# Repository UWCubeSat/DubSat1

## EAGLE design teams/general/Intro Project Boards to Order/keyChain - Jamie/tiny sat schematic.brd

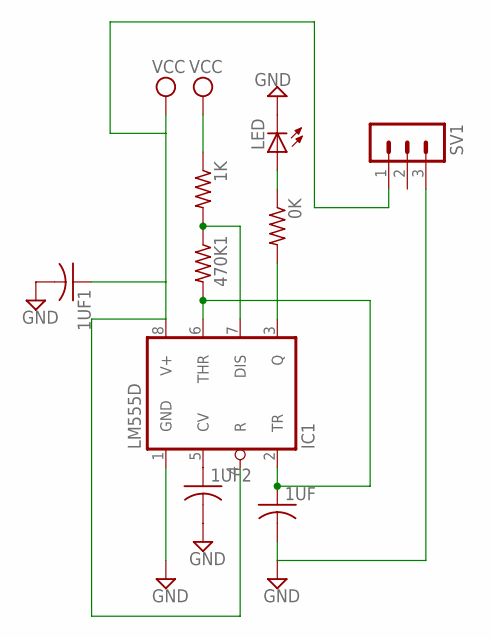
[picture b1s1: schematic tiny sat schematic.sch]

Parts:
0K, 1K, 470K1: R-US_R0805; R0805
1UF, 1UF1, 1UF2: C-USC0805; C0805
IC1: LM555D; SO08
LED: LED_ELD260; LED_LD260
SV1: MA03-1

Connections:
0: 1UF.1, 470K1.2, IC1.2 (TR), IC1.6 (THR)
470K: 0K.2, IC1.3 (Q)
GND: 1UF.2, 1UF1.2, 1UF2.2, IC1.1 (GND), LED.K (C), SV1.3
unnamed: 1K.2, 470K1.1, IC1.7 (DIS)
unnamed: 1UF2.1, IC1.5 (CV)
unnamed: 0K.1, LED.A
VCC: 1K.1, 1UF1.1, IC1.4 (R), IC1.8 (V+), SV1.1

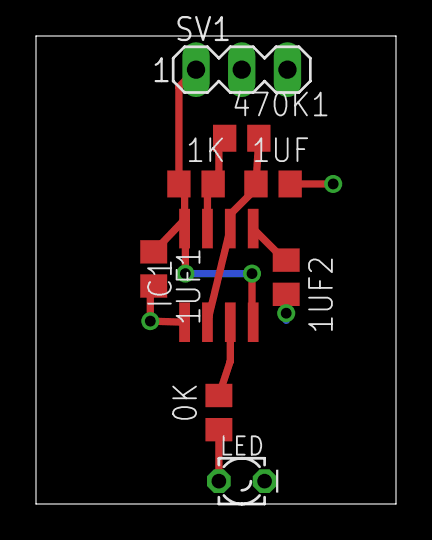
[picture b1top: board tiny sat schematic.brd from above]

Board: 2 copper layers, 20.0 x 26.0 mm, 9 parts (0 on the bottom side), 7 nets.

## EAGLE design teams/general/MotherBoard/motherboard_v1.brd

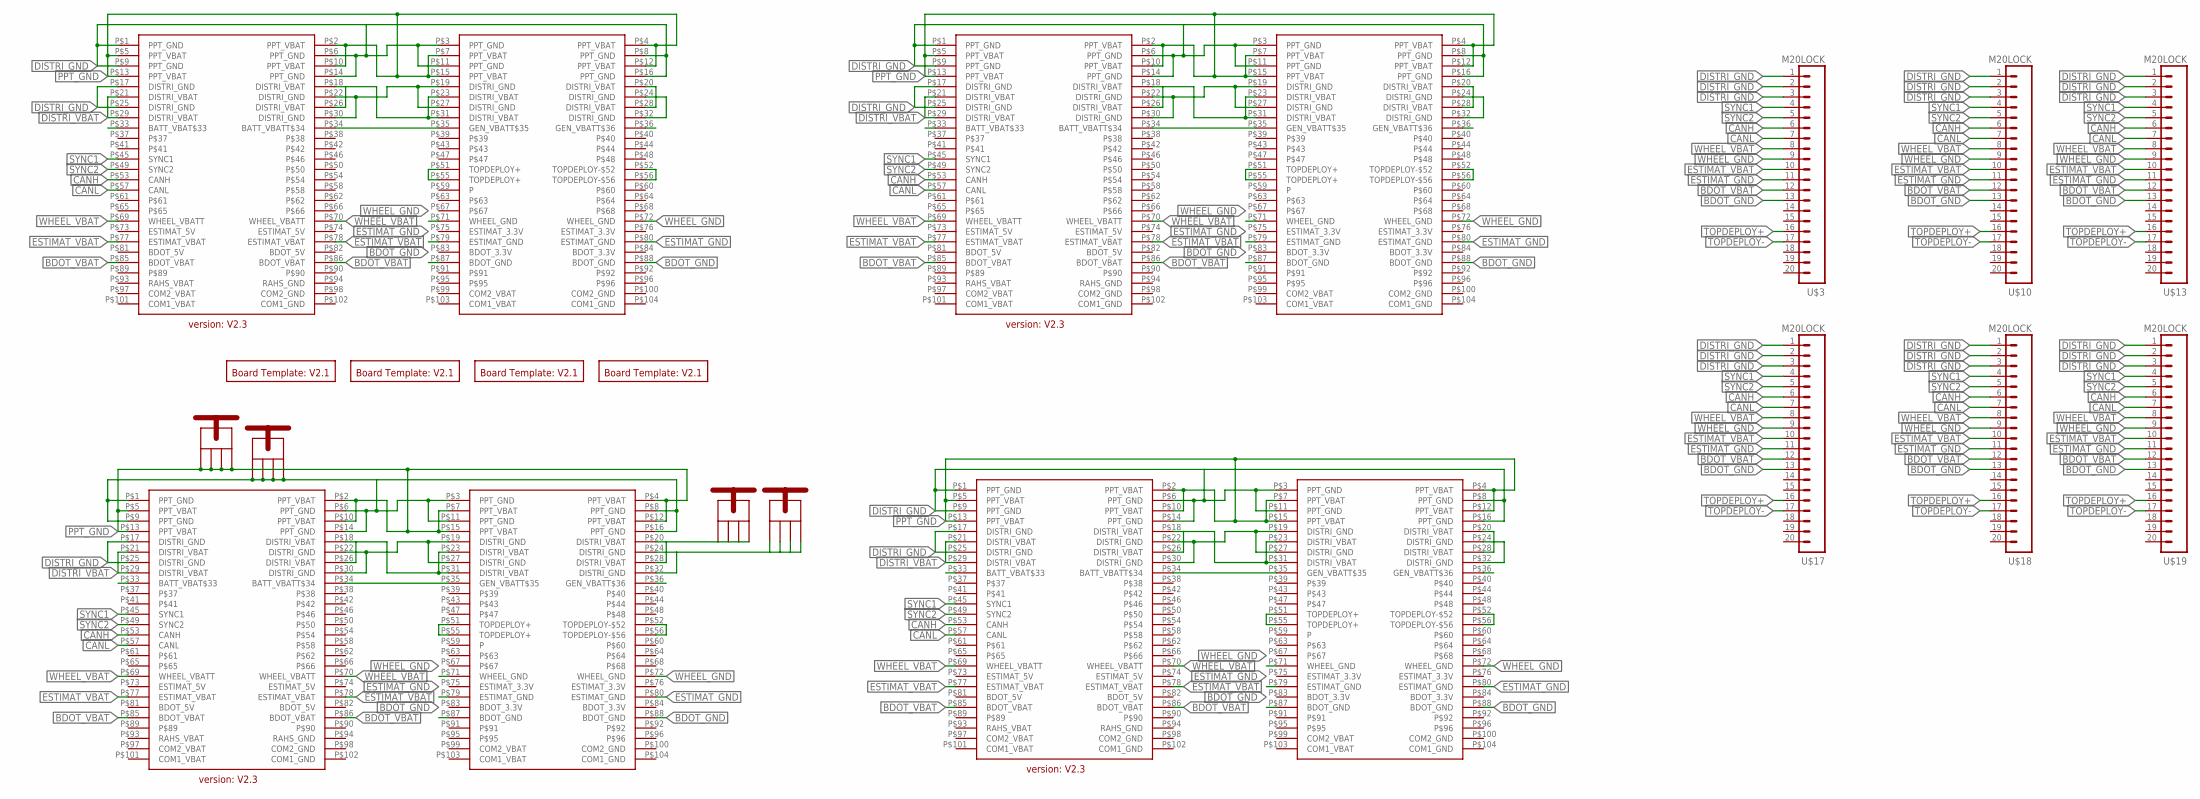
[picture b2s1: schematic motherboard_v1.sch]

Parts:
JP1, JP2, JP9, JP10: KEYSTONE_SCREW_TERMINAL_7701; 7701
U$1, U$4, U$5, U$6: BOARD_TEMPLATESILKONLY; BOARD_TEMPLATE_SILKONLY
U$2, U$7, U$9, U$11: PC104_CONNECTOR
U$3, U$10, U$13, U$17, U$18, U$19: M20LOCK; 1X20_LOCK

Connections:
BDOT_GND: U$2.P$87 (BDOT_GND), U$2.P$88 (BDOT_GND), U$3.13, U$7.P$87 (BDOT_GND), U$7.P$88 (BDOT_GND), U$9.P$87 (BDOT_GND), U$9.P$88 (BDOT_GND), U$10.13, U$11.P$87 (BDOT_GND), U$11.P$88 (BDOT_GND), U$13.13, U$17.13, U$18.13, U$19.13
BDOT_VBAT: U$2.P$85 (BDOT_VBAT), U$2.P$86 (BDOT_VBAT), U$3.12, U$7.P$85 (BDOT_VBAT), U$7.P$86 (BDOT_VBAT), U$9.P$85 (BDOT_VBAT), U$9.P$86 (BDOT_VBAT), U$10.12, U$11.P$85 (BDOT_VBAT), U$11.P$86 (BDOT_VBAT), U$13.12, U$17.12, U$18.12, U$19.12
CANH: U$2.P$53 (CANH), U$3.6, U$7.P$53 (CANH), U$9.P$53 (CANH), U$10.6, U$11.P$53 (CANH), U$13.6, U$17.6, U$18.6, U$19.6
CANL: U$2.P$57 (CANL), U$3.7, U$7.P$57 (CANL), U$9.P$57 (CANL), U$10.7, U$11.P$57 (CANL), U$13.7, U$17.7, U$18.7, U$19.7
DISTRI_GND: JP2.P$1, JP2.P$2, JP2.P$3, JP2.P$4, JP10.P$1, JP10.P$2, JP10.P$3, JP10.P$4, U$2.P$1 (PPT_GND), U$2.P$3 (PPT_GND), U$2.P$6 (PPT_GND), U$2.P$8 (PPT_GND), U$2.P$9 (PPT_GND), U$2.P$11 (PPT_GND), U$2.P$14 (PPT_GND), U$2.P$16 (PPT_GND), U$2.P$17 (DISTRI_GND), U$2.P$19 (DISTRI_GND), U$2.P$22 (DISTRI_GND), U$2.P$24 (DISTRI_GND), U$2.P$25 (DISTRI_GND), U$2.P$27 (DISTRI_GND), U$2.P$30 (DISTRI_GND), U$2.P$32 (DISTRI_GND), U$3.1, U$3.2, U$3.3, U$7.P$1 (PPT_GND), U$7.P$3 (PPT_GND), U$7.P$6 (PPT_GND), U$7.P$8 (PPT_GND), U$7.P$9 (PPT_GND), U$7.P$11 (PPT_GND), U$7.P$14 (PPT_GND), U$7.P$16 (PPT_GND), U$7.P$17 (DISTRI_GND), U$7.P$19 (DISTRI_GND), U$7.P$22 (DISTRI_GND), U$7.P$24 (DISTRI_GND), U$7.P$25 (DISTRI_GND), U$7.P$27 (DISTRI_GND), U$7.P$30 (DISTRI_GND), U$7.P$32 (DISTRI_GND), U$9.P$1 (PPT_GND), U$9.P$3 (PPT_GND), U$9.P$6 (PPT_GND), U$9.P$8 (PPT_GND), U$9.P$9 (PPT_GND), U$9.P$11 (PPT_GND), U$9.P$14 (PPT_GND), U$9.P$16 (PPT_GND), U$9.P$17 (DISTRI_GND), U$9.P$19 (DISTRI_GND), U$9.P$22 (DISTRI_GND), U$9.P$24 (DISTRI_GND), U$9.P$25 (DISTRI_GND), U$9.P$27 (DISTRI_GND), U$9.P$30 (DISTRI_GND), U$9.P$32 (DISTRI_GND), U$10.1, U$10.2, U$10.3, U$11.P$1 (PPT_GND), U$11.P$3 (PPT_GND), U$11.P$6 (PPT_GND), U$11.P$8 (PPT_GND), U$11.P$9 (PPT_GND), U$11.P$11 (PPT_GND), U$11.P$14 (PPT_GND), U$11.P$16 (PPT_GND), U$11.P$17 (DISTRI_GND), U$11.P$19 (DISTRI_GND), U$11.P$22 (DISTRI_GND), U$11.P$24 (DISTRI_GND), U$11.P$25 (DISTRI_GND), U$11.P$27 (DISTRI_GND), U$11.P$30 (DISTRI_GND), U$11.P$32 (DISTRI_GND), U$13.1, U$13.2, U$13.3, U$17.1, U$17.2, U$17.3, U$18.1, U$18.2, U$18.3, U$19.1, U$19.2, U$19.3
DISTRI_VBAT: JP1.P$1, JP1.P$2, JP1.P$3, JP1.P$4, U$2.P$18 (DISTRI_VBAT), U$2.P$20 (DISTRI_VBAT), U$2.P$21 (DISTRI_VBAT), U$2.P$23 (DISTRI_VBAT), U$2.P$26 (DISTRI_VBAT), U$2.P$28 (DISTRI_VBAT), U$2.P$29 (DISTRI_VBAT), U$2.P$31 (DISTRI_VBAT), U$7.P$18 (DISTRI_VBAT), U$7.P$20 (DISTRI_VBAT), U$7.P$21 (DISTRI_VBAT), U$7.P$23 (DISTRI_VBAT), U$7.P$26 (DISTRI_VBAT), U$7.P$28 (DISTRI_VBAT), U$7.P$29 (DISTRI_VBAT), U$7.P$31 (DISTRI_VBAT), U$9.P$18 (DISTRI_VBAT), U$9.P$20 (DISTRI_VBAT), U$9.P$21 (DISTRI_VBAT), U$9.P$23 (DISTRI_VBAT), U$9.P$26 (DISTRI_VBAT), U$9.P$28 (DISTRI_VBAT), U$9.P$29 (DISTRI_VBAT), U$9.P$31 (DISTRI_VBAT), U$11.P$18 (DISTRI_VBAT), U$11.P$20 (DISTRI_VBAT), U$11.P$21 (DISTRI_VBAT), U$11.P$23 (DISTRI_VBAT), U$11.P$26 (DISTRI_VBAT), U$11.P$28 (DISTRI_VBAT), U$11.P$29 (DISTRI_VBAT), U$11.P$31 (DISTRI_VBAT)
EPS: U$2.P$33 (BATT_VBAT$33), U$2.P$34 (BATT_VBATT$34), U$2.P$35 (GEN_VBATT$35), U$2.P$36 (GEN_VBATT$36), U$7.P$33 (BATT_VBAT$33), U$7.P$34 (BATT_VBATT$34), U$7.P$35 (GEN_VBATT$35), U$7.P$36 (GEN_VBATT$36), U$9.P$33 (BATT_VBAT$33), U$9.P$34 (BATT_VBATT$34), U$9.P$35 (GEN_VBATT$35), U$9.P$36 (GEN_VBATT$36), U$11.P$33 (BATT_VBAT$33), U$11.P$34 (BATT_VBATT$34), U$11.P$35 (GEN_VBATT$35), U$11.P$36 (GEN_VBATT$36)
ESTIMAT_GND: U$2.P$79 (ESTIMAT_GND), U$2.P$80 (ESTIMAT_GND), U$3.11, U$7.P$79 (ESTIMAT_GND), U$7.P$80 (ESTIMAT_GND), U$9.P$79 (ESTIMAT_GND), U$9.P$80 (ESTIMAT_GND), U$10.11, U$11.P$79 (ESTIMAT_GND), U$11.P$80 (ESTIMAT_GND), U$13.11, U$17.11, U$18.11, U$19.11
ESTIMAT_VBAT: U$2.P$77 (ESTIMAT_VBAT), U$2.P$78 (ESTIMAT_VBAT), U$3.10, U$7.P$77 (ESTIMAT_VBAT), U$7.P$78 (ESTIMAT_VBAT), U$9.P$77 (ESTIMAT_VBAT), U$9.P$78 (ESTIMAT_VBAT), U$10.10, U$11.P$77 (ESTIMAT_VBAT), U$11.P$78 (ESTIMAT_VBAT), U$13.10, U$17.10, U$18.10, U$19.10
PPT_GND: JP9.P$1, JP9.P$2, JP9.P$3, JP9.P$4, U$2.P$2 (PPT_VBAT), U$2.P$4 (PPT_VBAT), U$2.P$5 (PPT_VBAT), U$2.P$7 (PPT_VBAT), U$2.P$10 (PPT_VBAT), U$2.P$12 (PPT_VBAT), U$2.P$13 (PPT_VBAT), U$2.P$15 (PPT_VBAT), U$7.P$2 (PPT_VBAT), U$7.P$4 (PPT_VBAT), U$7.P$5 (PPT_VBAT), U$7.P$7 (PPT_VBAT), U$7.P$10 (PPT_VBAT), U$7.P$12 (PPT_VBAT), U$7.P$13 (PPT_VBAT), U$7.P$15 (PPT_VBAT), U$9.P$2 (PPT_VBAT), U$9.P$4 (PPT_VBAT), U$9.P$5 (PPT_VBAT), U$9.P$7 (PPT_VBAT), U$9.P$10 (PPT_VBAT), U$9.P$12 (PPT_VBAT), U$9.P$13 (PPT_VBAT), U$9.P$15 (PPT_VBAT), U$11.P$2 (PPT_VBAT), U$11.P$4 (PPT_VBAT), U$11.P$5 (PPT_VBAT), U$11.P$7 (PPT_VBAT), U$11.P$10 (PPT_VBAT), U$11.P$12 (PPT_VBAT), U$11.P$13 (PPT_VBAT), U$11.P$15 (PPT_VBAT)
SYNC1: U$2.P$45 (SYNC1), U$3.4, U$7.P$45 (SYNC1), U$9.P$45 (SYNC1), U$10.4, U$11.P$45 (SYNC1), U$13.4, U$17.4, U$18.4, U$19.4
SYNC2: U$2.P$49 (SYNC2), U$3.5, U$7.P$49 (SYNC2), U$9.P$49 (SYNC2), U$10.5, U$11.P$49 (SYNC2), U$13.5, U$17.5, U$18.5, U$19.5
TOPDEPLOY+: U$2.P$51 (TOPDEPLOY+), U$2.P$55 (TOPDEPLOY+), U$3.16, U$7.P$51 (TOPDEPLOY+), U$7.P$55 (TOPDEPLOY+), U$9.P$51 (TOPDEPLOY+), U$9.P$55 (TOPDEPLOY+), U$10.16, U$11.P$51 (TOPDEPLOY+), U$11.P$55 (TOPDEPLOY+), U$13.16, U$17.16, U$18.16, U$19.16
TOPDEPLOY-: U$2.P$52 (TOPDEPLOY-$52), U$2.P$56 (TOPDEPLOY-$56), U$3.17, U$7.P$52 (TOPDEPLOY-$52), U$7.P$56 (TOPDEPLOY-$56), U$9.P$52 (TOPDEPLOY-$52), U$9.P$56 (TOPDEPLOY-$56), U$10.17, U$11.P$52 (TOPDEPLOY-$52), U$11.P$56 (TOPDEPLOY-$56), U$13.17, U$17.17, U$18.17, U$19.17
WHEEL_GND: U$2.P$71 (WHEEL_GND), U$2.P$72 (WHEEL_GND), U$3.9, U$7.P$71 (WHEEL_GND), U$7.P$72 (WHEEL_GND), U$9.P$71 (WHEEL_GND), U$9.P$72 (WHEEL_GND), U$10.9, U$11.P$71 (WHEEL_GND), U$11.P$72 (WHEEL_GND), U$13.9, U$17.9, U$18.9, U$19.9
WHEEL_VBAT: U$2.P$69 (WHEEL_VBATT), U$2.P$70 (WHEEL_VBATT), U$3.8, U$7.P$69 (WHEEL_VBATT), U$7.P$70 (WHEEL_VBATT), U$9.P$69 (WHEEL_VBATT), U$9.P$70 (WHEEL_VBATT), U$10.8, U$11.P$69 (WHEEL_VBATT), U$11.P$70 (WHEEL_VBATT), U$13.8, U$17.8, U$18.8, U$19.8

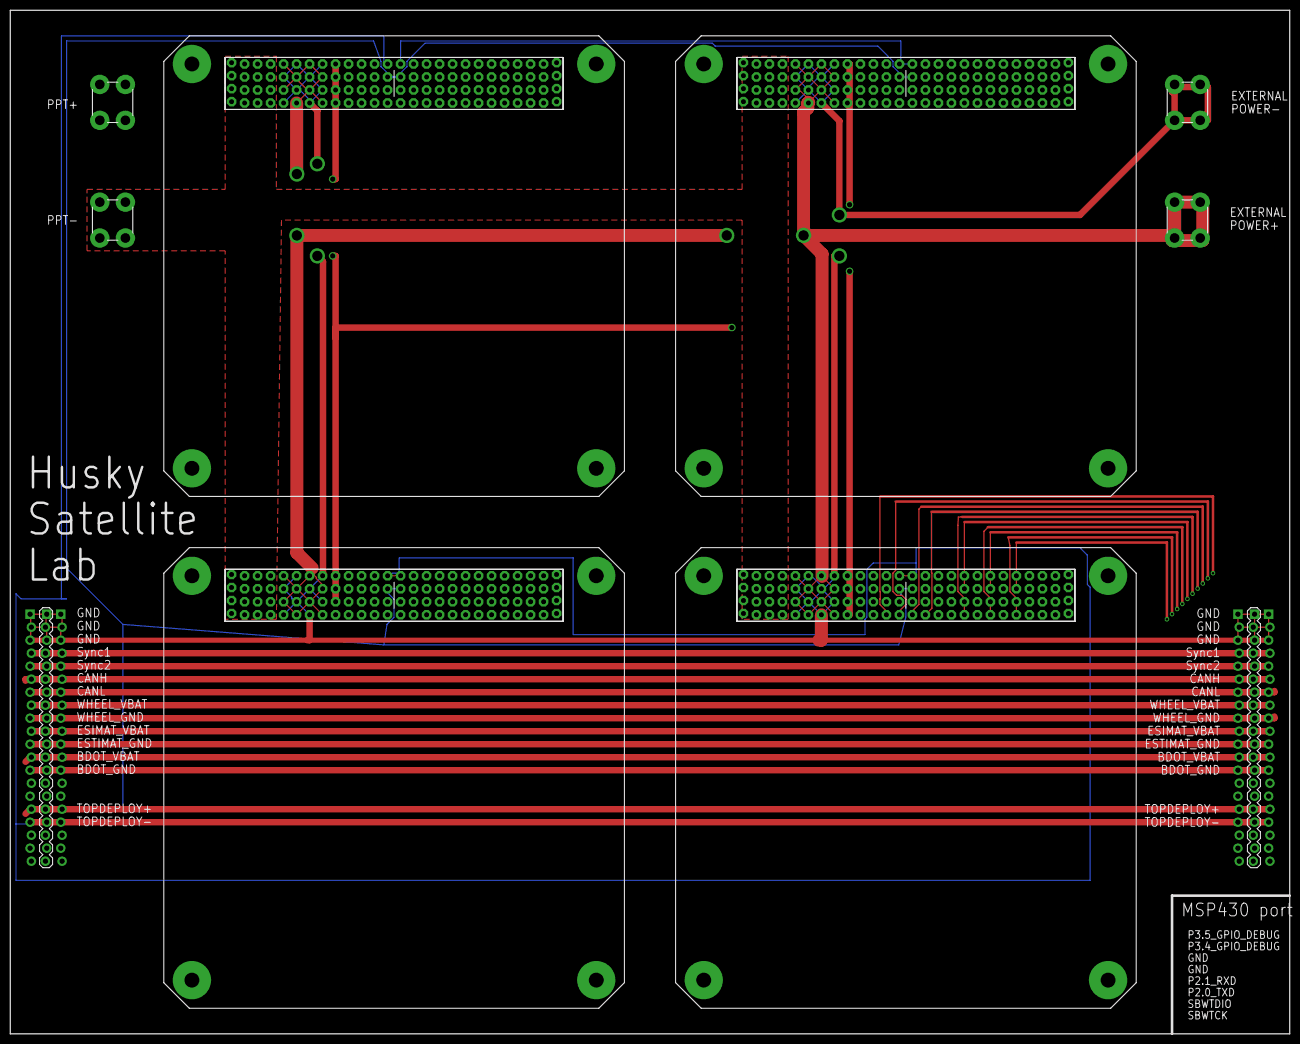
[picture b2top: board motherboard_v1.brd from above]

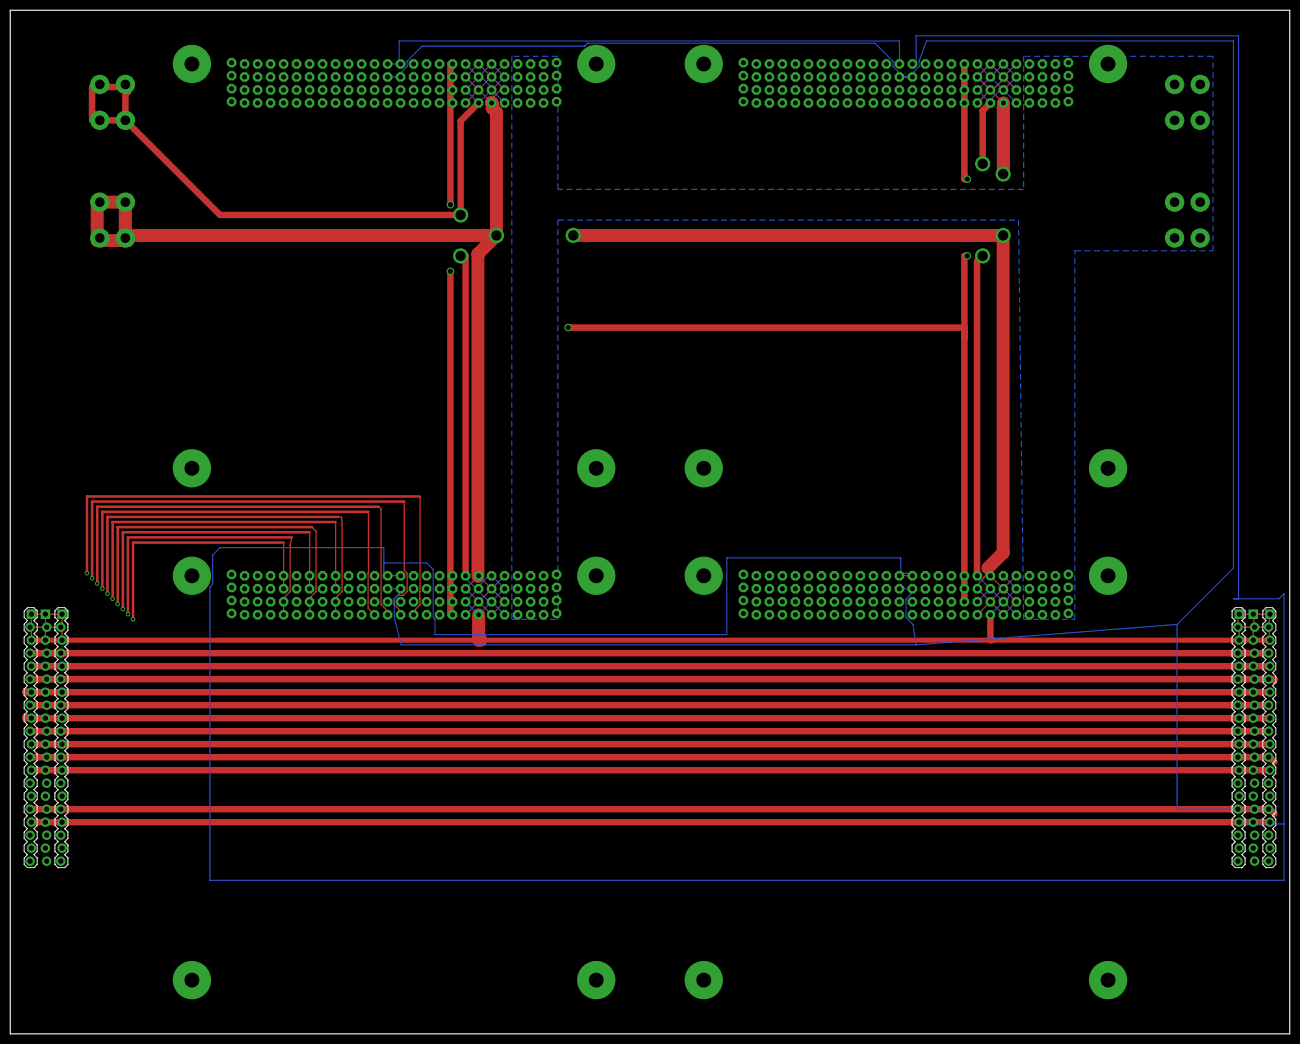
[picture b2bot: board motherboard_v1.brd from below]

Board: 4 copper layers, 250.0 x 200.0 mm, 18 parts (4 on the bottom side), 16 nets.

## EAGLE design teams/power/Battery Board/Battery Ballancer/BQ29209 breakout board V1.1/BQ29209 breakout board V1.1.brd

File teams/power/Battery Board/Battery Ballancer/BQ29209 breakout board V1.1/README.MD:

This is an ordered board, please do not change.

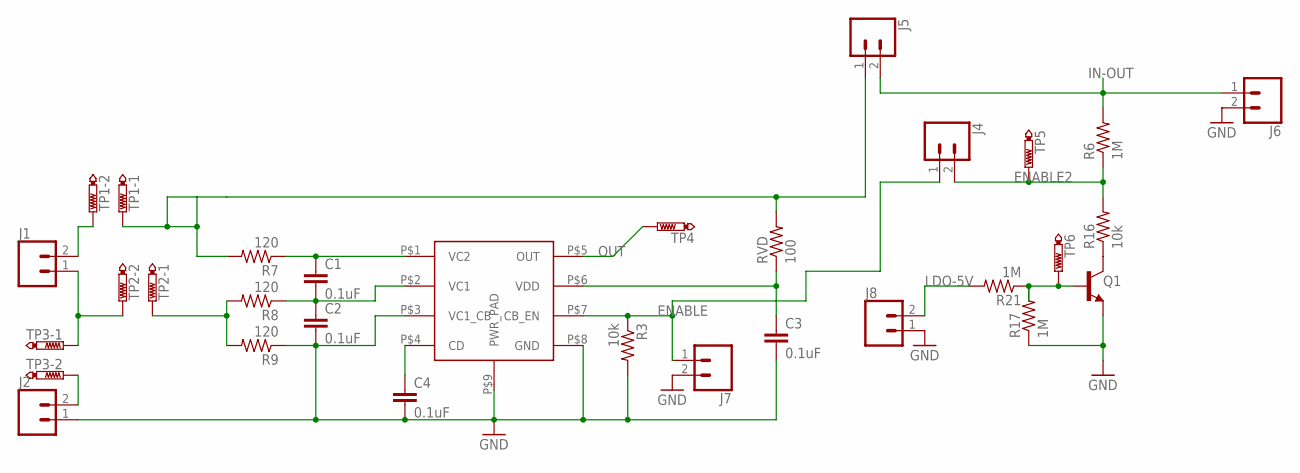
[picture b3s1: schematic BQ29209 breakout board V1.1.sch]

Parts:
C1, C2, C3, C4: 0.1uF; C0805
J1, J2, J4, J5, J6, J7, J8: CONN_02; 1X02
Q1: TRANS_NPN-MMBT2222AL; SOT23-3
R3, R16: 10k; R0805
R6: 1M; R0805
R7, R8, R9: 120; R0805
R17, R21: 1M; M0805
RVD: 100; R0805
TP1, TP2, TP3: PTR2; P2-38-17
TP4, TP5, TP6: PTR1PAD1-13Y; P1-13Y
U$8: BQ29209; VSON8

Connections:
BASE: Q1.1 (B), R17.2, R21.1, TP6.TP
ENABLE: J4.1, J7.1, R3.1, U$8.P$7 (CB_EN)
ENABLE2: J4.2, R6.1, R16.2, TP5.TP
GND: C2.2, C3.2, C4.2, J2.1, J6.2, J7.2, J8.1, Q1.2 (E), R3.2, R9.1, R17.1, U$8.P$3 (VC1_CB), U$8.P$8 (GND), U$8.P$9 (PWR_PAD)
IN-OUT: J5.2, J6.1, R6.2
LDO-5V: J8.2, R21.2
unnamed: J1.2, TP1.TP-2
unnamed: R8.2, R9.2, TP2.TP-1
unnamed: J1.1, TP2.TP-2, TP3.TP-1
unnamed: C1.1, R7.1, U$8.P$1 (VC2)
unnamed: C1.2, C2.1, R8.1, U$8.P$2 (VC1)
unnamed: C3.1, RVD.1, U$8.P$6 (VDD)
unnamed: Q1.3 (C), R16.1
unnamed: C4.1, U$8.P$4 (CD)
unnamed: J2.2, TP3.TP-2
OUT: TP4.TP, U$8.P$5 (OUT)
V-BATT: J5.1, R7.2, RVD.2, TP1.TP-1

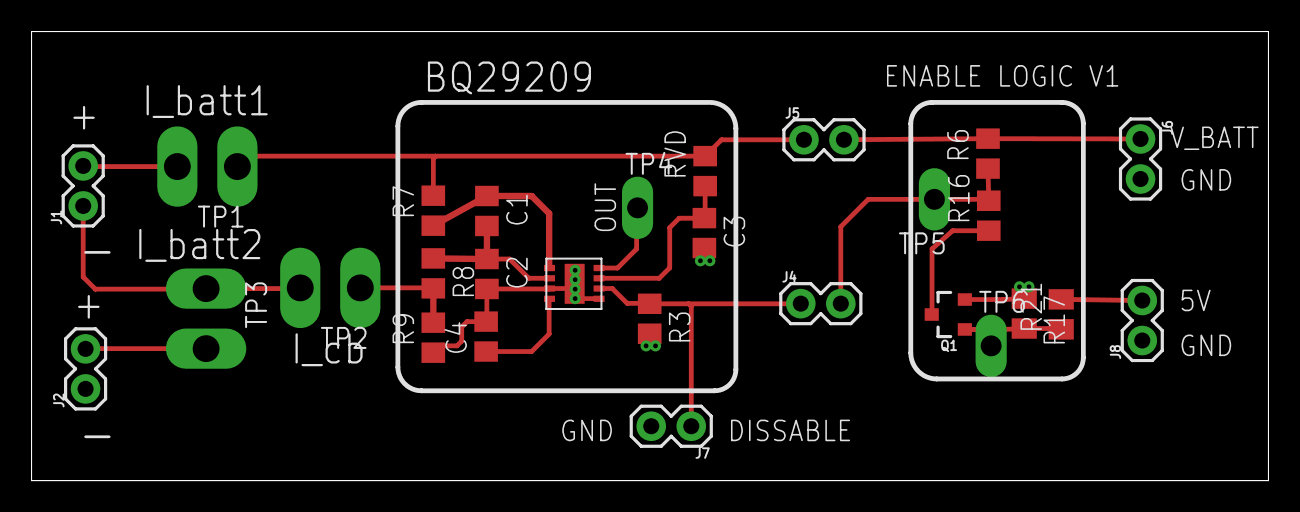
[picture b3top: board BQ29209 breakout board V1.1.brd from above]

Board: 2 copper layers, 78.5 x 28.5 mm, 28 parts (0 on the bottom side), 17 nets.

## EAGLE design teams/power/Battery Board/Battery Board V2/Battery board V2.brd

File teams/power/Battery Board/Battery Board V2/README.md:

This is an ordered board, do not modify. See a more recent version.

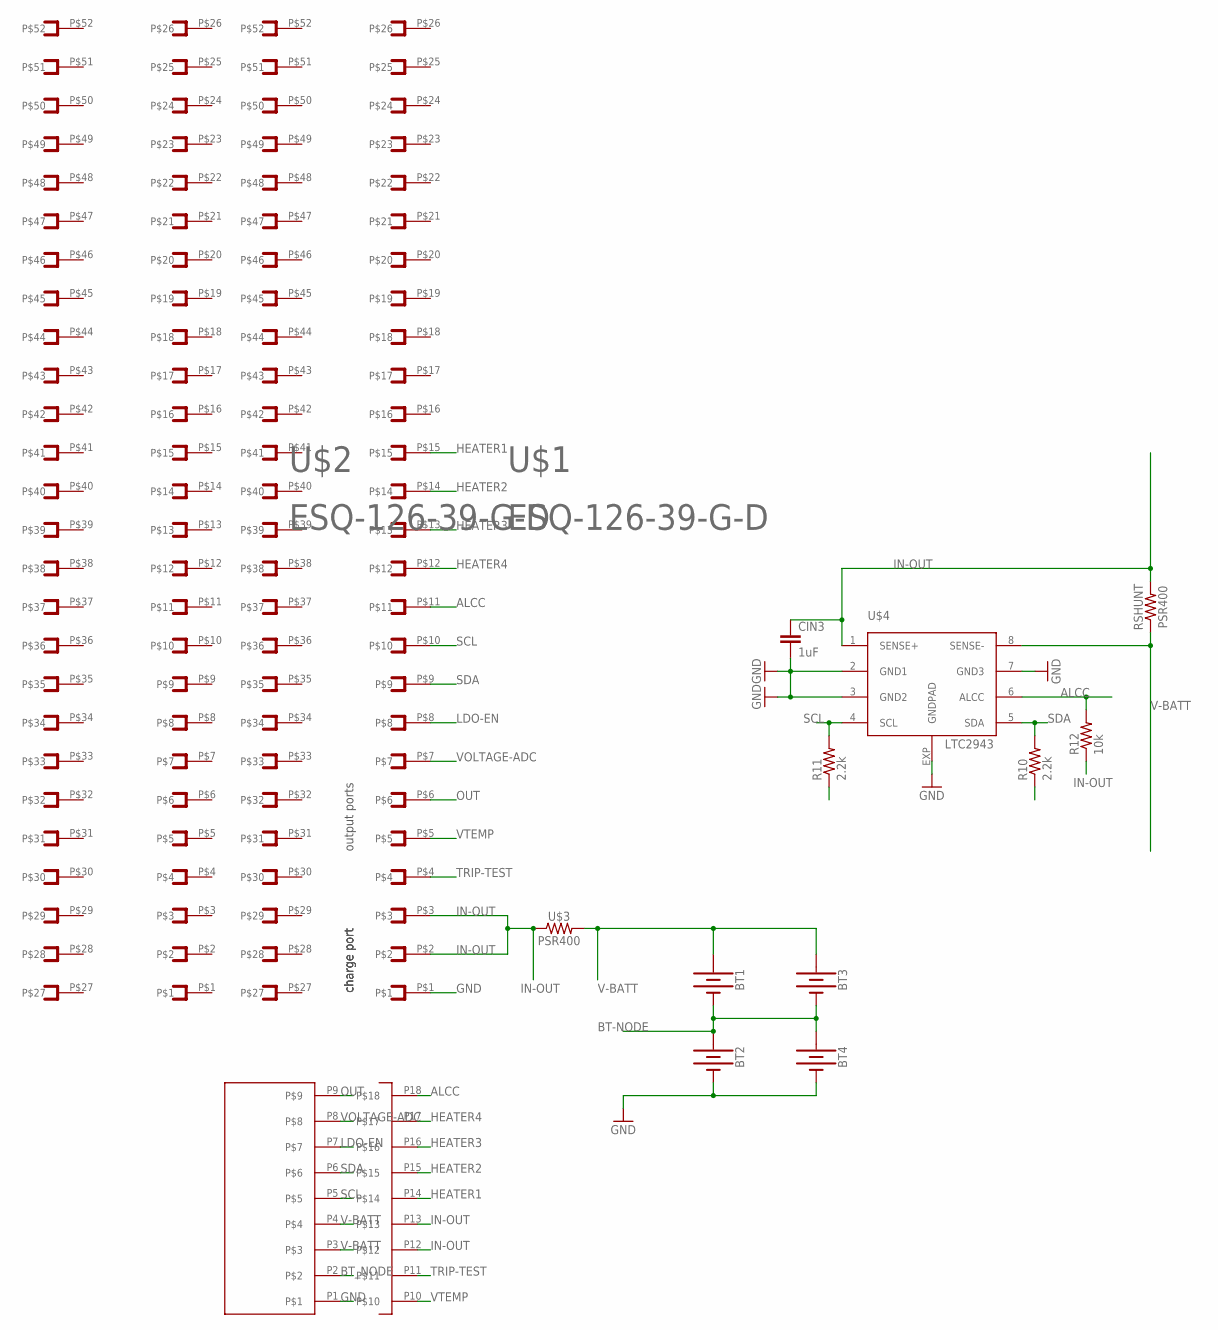
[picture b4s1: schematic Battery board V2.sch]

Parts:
BT1, BT2, BT3, BT4: BATTERY-18650; BATTERY_18650-HOLDER
CIN3: 1uF; 0402-CAP
R10, R11: 2.2k; R0805
R12: 10k; R0805
RSHUNT: PSR400
U$1, U$2: ESQ-126-39-G-D; (RD)ESQ-126-39-G-D
U$3: PSR400
U$4: LTC2943; DFN8(3X3)LT
U$7: FFC18

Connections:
ALCC: R12.2, U$1.P$11, U$4.6 (ALCC), U$7.P18
BT-NODE: BT1.GND@1 (-), BT2.PWR@1 (+), BT3.GND@1 (-), BT4.PWR@1 (+)
BT_NODE: U$7.P2
GND: BT2.GND@1 (-), BT4.GND@1 (-), CIN3.2, U$1.P$1, U$4.2 (GND1), U$4.3 (GND2), U$4.7 (GND3), U$4.EXP (GNDPAD), U$7.P1
HEATER1: U$1.P$15, U$7.P14
HEATER2: U$1.P$14, U$7.P15
HEATER3: U$1.P$13, U$7.P16
HEATER4: U$1.P$12, U$7.P17
IN-OUT: CIN3.1, R10.1, R11.1, R12.1, RSHUNT.P$2 (2), U$1.P$2, U$1.P$3, U$3.P$1 (1), U$4.1 (SENSE+), U$7.P12, U$7.P13
LDO-EN: U$1.P$8, U$7.P7
OUT: U$1.P$6, U$7.P9
SCL: R11.2, U$1.P$10, U$4.4 (SCL), U$7.P5
SDA: R10.2, U$1.P$9, U$4.5 (SDA), U$7.P6
TRIP-TEST: U$1.P$4, U$7.P11
V-BATT: BT1.PWR@1 (+), BT3.PWR@1 (+), RSHUNT.P$1 (1), U$3.P$2 (2), U$4.8 (SENSE-), U$7.P3, U$7.P4
VOLTAGE-ADC: U$1.P$7, U$7.P8
VTEMP: U$1.P$5, U$7.P10

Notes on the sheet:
charge port
output ports

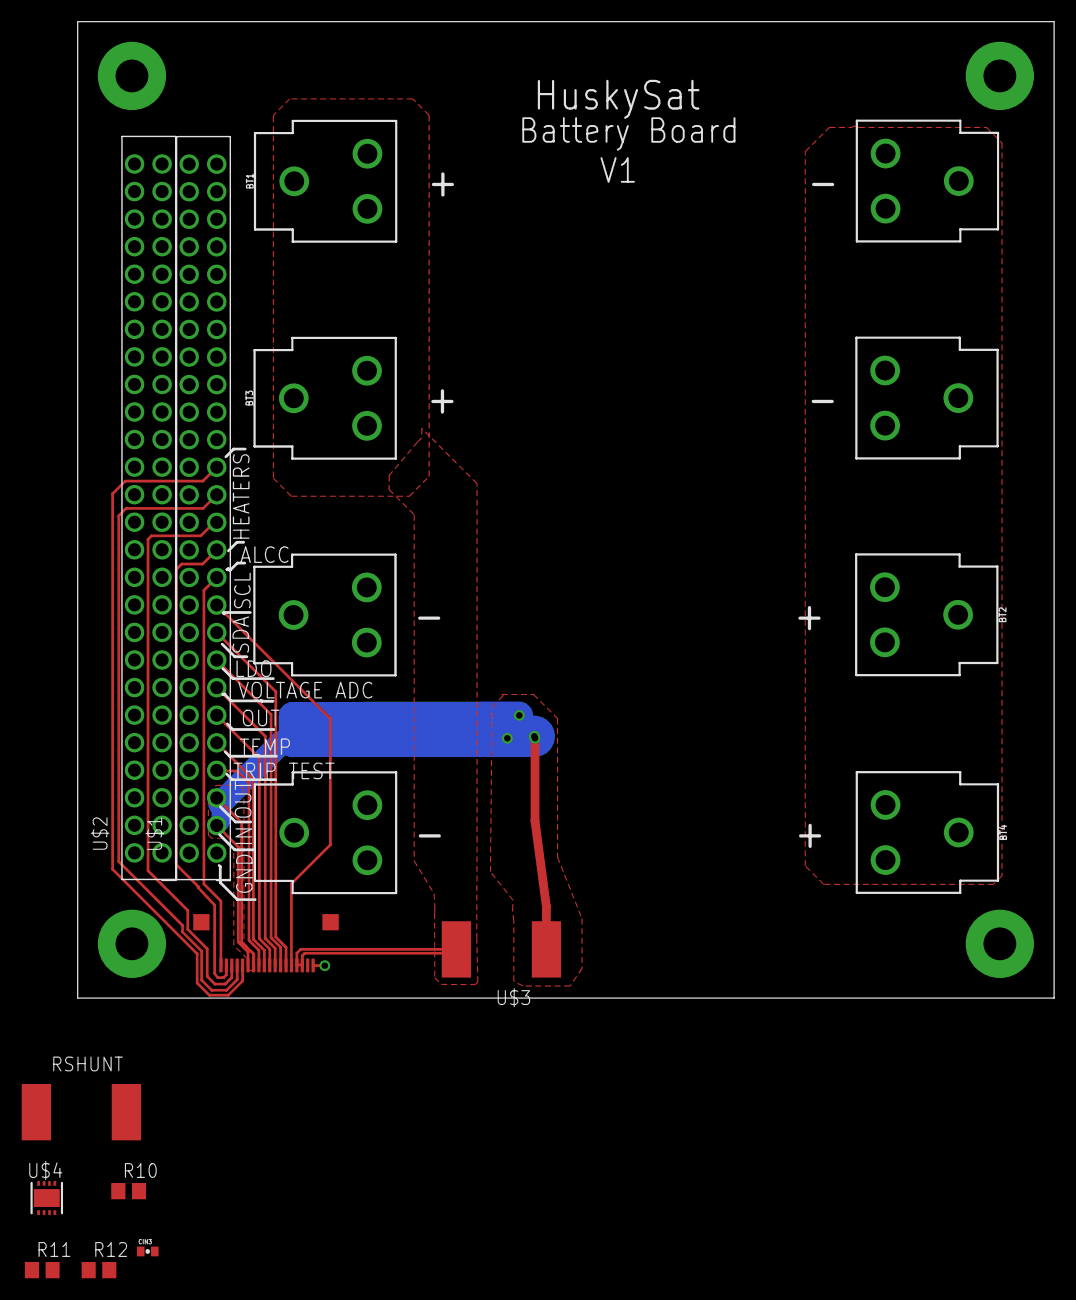
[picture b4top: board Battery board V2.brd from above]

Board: 2 copper layers, 90.0 x 90.0 mm, 14 parts (0 on the bottom side), 16 nets.

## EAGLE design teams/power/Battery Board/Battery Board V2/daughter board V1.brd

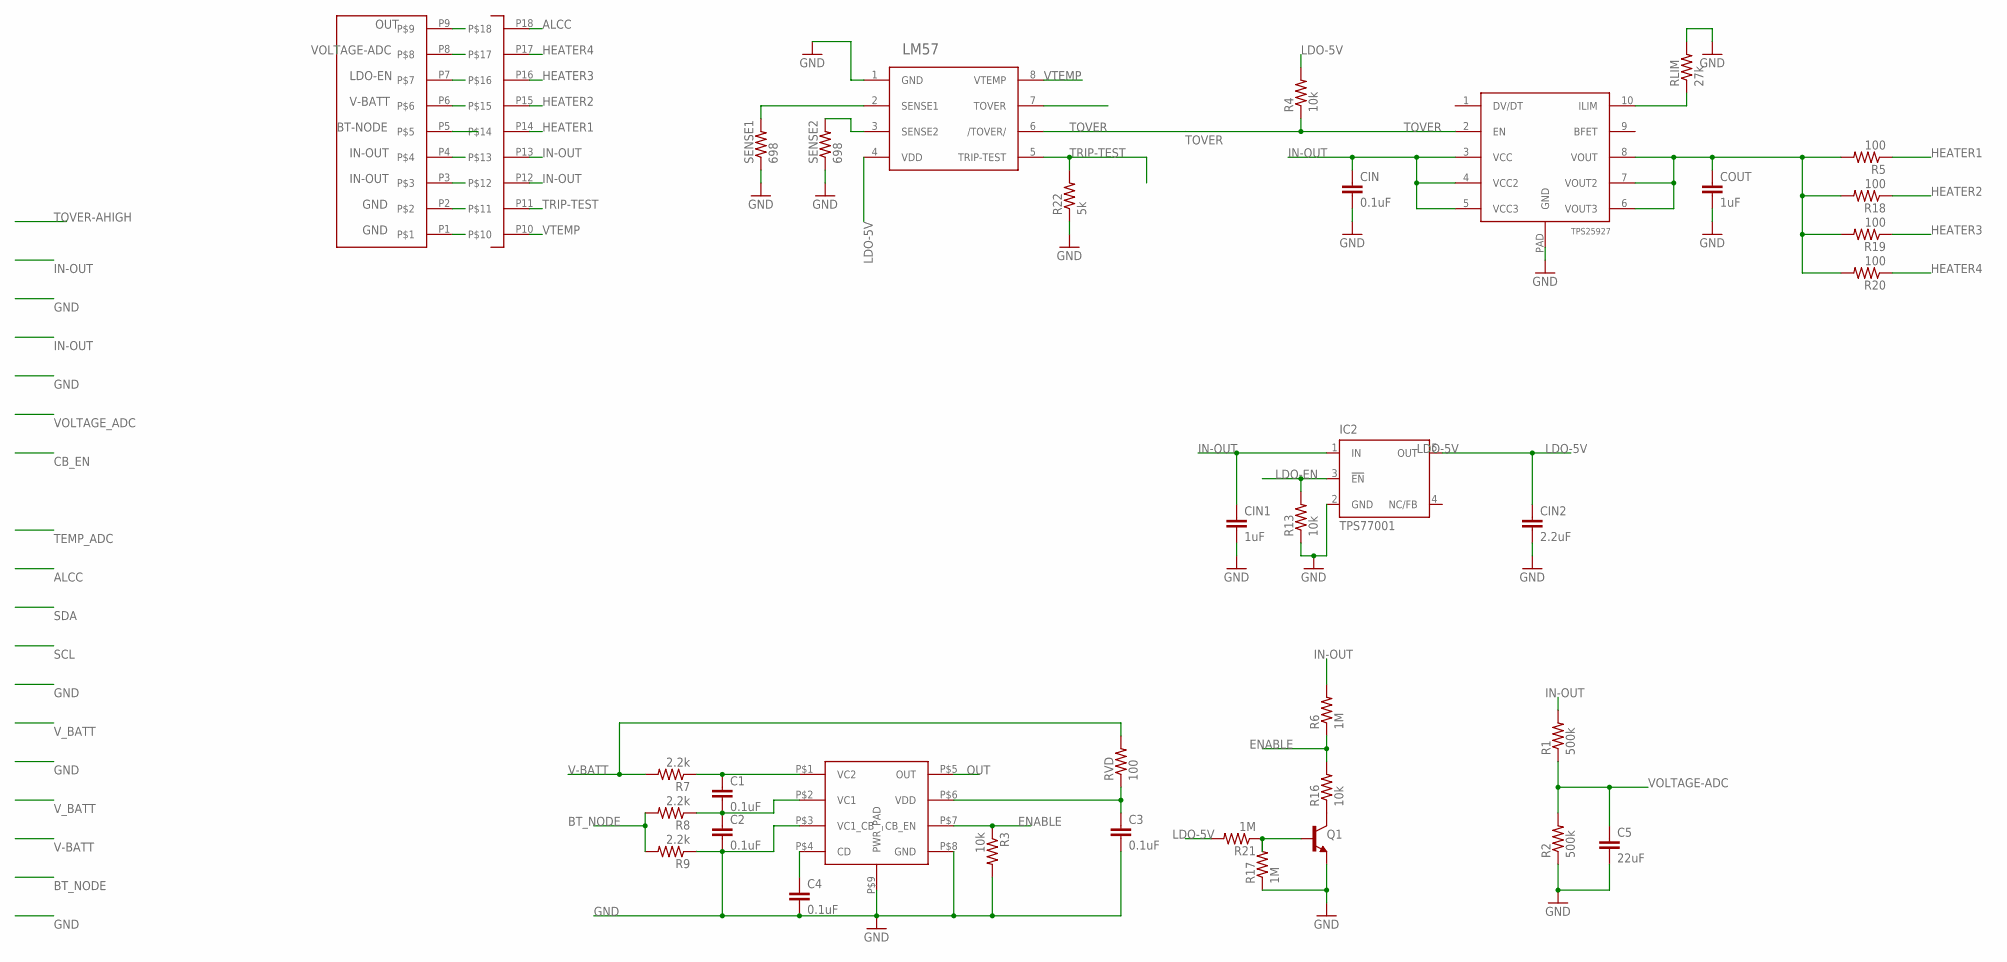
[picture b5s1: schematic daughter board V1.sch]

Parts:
C1, C2, C3, C4: 0.1uF; 0402-CAP
C5: 22uF; C1206
CIN: 0.1uF; 0402-CAP
CIN1: 1uF; 0402-CAP
CIN2: 2.2uF; 0402-CAP
COUT: 1uF; 0402-CAP
IC2: TPS77001; SOT23-DBV
Q1: TRANS_NPN-MMBT2222AL; SOT23-3
R1, R2: 500k; R0805
R3, R4, R13, R16: 10k; R0805
R5, R18, R19, R20: 100; R0805
R6: 1M; R0805
R7, R8, R9: 2.2k; R0805
R17, R21: 1M; M0805
R22: 5k; R0805
RLIM: 27k; R0805
RVD: 100; R0805
SENSE1, SENSE2: 698; R0805
U$2: LM57; TSSOP-8
U$5: TPS252927; VSON10
U$7: FFC18
U$8: BQ29209; VSON8

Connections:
ALCC: U$7.P18
BASE: Q1.1 (B), R17.2, R21.1
BT-NODE: U$7.P5
BT_NODE: R8.2, R9.2
ENABLE: R3.1, R6.1, R16.2, U$8.P$7 (CB_EN)
GND: C2.2, C3.2, C4.2, C5.2, CIN.2, CIN1.2, CIN2.2, COUT.2, IC2.2 (GND), Q1.2 (E), R2.1, R3.2, R9.1, R13.1, R17.1, R22.1, RLIM.2, SENSE1.1, SENSE2.1, U$2.1 (GND), U$5.PAD (GND), U$7.P1, U$7.P2, U$8.P$3 (VC1_CB), U$8.P$8 (GND), U$8.P$9 (PWR_PAD)
HEATER1: R5.1, U$7.P14
HEATER2: R18.1, U$7.P15
HEATER3: R19.1, U$7.P16
HEATER4: R20.1, U$7.P17
IN-OUT: CIN.1, CIN1.1, IC2.1 (IN), R1.2, R6.2, U$5.3 (VCC), U$5.4 (VCC2), U$5.5 (VCC3), U$7.P3, U$7.P4, U$7.P12, U$7.P13
LDO-5V: CIN2.1, IC2.5 (OUT), R4.2, R21.2, U$2.4 (VDD)
LDO-EN: IC2.3 (!EN), R13.2, U$7.P7
unnamed: SENSE1.2, U$2.2 (SENSE1)
unnamed: C1.1, R7.1, U$8.P$1 (VC2)
unnamed: C1.2, C2.1, R8.1, U$8.P$2 (VC1)
unnamed: C3.1, RVD.1, U$8.P$6 (VDD)
unnamed: Q1.3 (C), R16.1
unnamed: C4.1, U$8.P$4 (CD)
unnamed: COUT.1, R5.2, R18.2, R19.2, R20.2, U$5.6 (VOUT3), U$5.7 (VOUT2), U$5.8 (VOUT)
unnamed: RLIM.1, U$5.10 (ILIM)
unnamed: SENSE2.2, U$2.3 (SENSE2)
OUT: U$7.P9, U$8.P$5 (OUT)
TOVER: R4.1, U$2.6 (/TOVER/), U$5.2 (EN)
TRIP-TEST: R22.2, U$2.5 (TRIP-TEST), U$7.P11
V-BATT: R7.2, RVD.2, U$7.P6
VOLTAGE-ADC: C5.1, R1.1, R2.2, U$7.P8
VTEMP: U$2.8 (VTEMP), U$7.P10

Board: 2 copper layers, 36 parts (1 on the bottom side), 26 nets, no tracks yet.

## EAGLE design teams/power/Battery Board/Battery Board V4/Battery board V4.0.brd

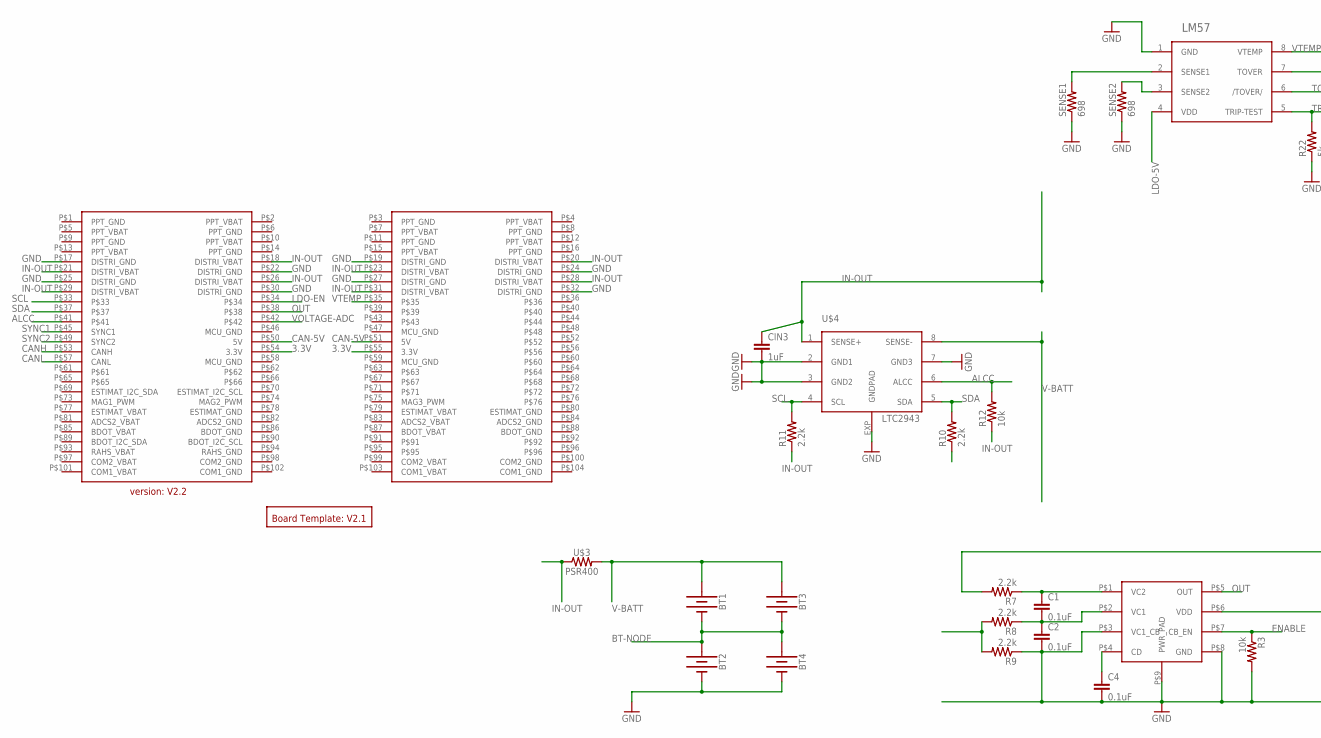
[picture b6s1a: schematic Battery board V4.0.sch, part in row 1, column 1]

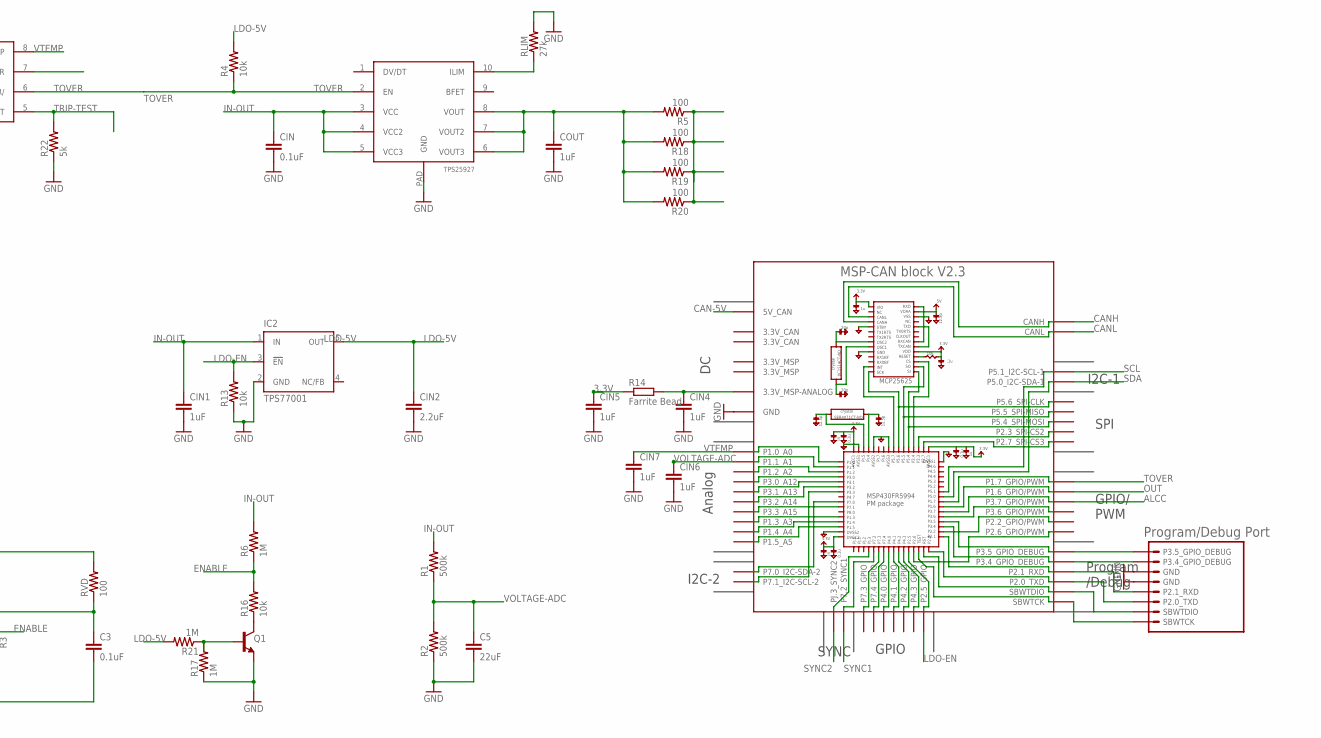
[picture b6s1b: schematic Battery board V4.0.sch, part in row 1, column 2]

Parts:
BT1, BT2, BT3, BT4: BATTERY-18650; BATTERY_18650-HOLDER
C1, C2, C3, C4: 0.1uF; C0805
C5: 22uF; C1206
CIN: 0.1uF; C0805
CIN1, CIN3, CIN4, CIN5, CIN6, CIN7: 1uF; C0805
CIN2: 2.2uF; C0805
COUT: 1uF; C0805
IC2: TPS77001; SOT23-DBV
Q1: TRANS_NPN-MMBT2222AL; SOT23-3
R1, R2: 500k; R0805
R3, R4, R12, R13, R16: 10k; R0805
R5, R18, R19, R20: 100; R0805
R6: 1M; R0805
R7, R8, R9, R10, R11: 2.2k; R0805
R14: Farrite Bead; R1206
R17, R21: 1M; M0805
R22: 5k; R0805
RLIM: 27k; R0805
RVD: 100; R0805
SENSE1, SENSE2: 698; R0805
U$1: MSP-CAN_BLOCK
U$2: PROGRAM/DEBUG_PORT; 1X08_CONNECTOR
U$3: PSR400
U$4: LTC2943; DFN8(3X3)LT
U$5: TPS252927; VSON10
U$6: LM57; TSSOP-8
U$7: 2X26_CONNECTOR_(V2.2); 4X26_CONNECTOR_(V2.2)
U$8: BQ29209; VSON8
U$9: BOARD_TEMPLATE_(V2.1)

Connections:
3.3V: CIN5.1, R14.1, U$7.P$54 (3.3V), U$7.P$55 (3.3V)
ALCC: R12.2, U$1.P3.7_GPIO/PWM, U$4.6 (ALCC), U$7.P$41
BASE: Q1.1 (B), R17.2, R21.1
BT-NODE: BT1.GND@1 (-), BT2.PWR@1 (+), BT3.GND@1 (-), BT4.PWR@1 (+), R8.2, R9.2
CAN-5V: U$1.5V (5V_CAN), U$7.P$50 (5V), U$7.P$51 (5V)
CANH: U$1.CANH, U$7.P$53 (CANH)
CANL: U$1.CANL, U$7.P$57 (CANL)
ENABLE: R3.1, R6.1, R16.2, U$8.P$7 (CB_EN)
FERRITE-BEAD: CIN4.1, R14.2, U$1.3.3V_ANALOG@MSP2 (3.3V_MSP-ANALOG)
GND: BT2.GND@1 (-), BT4.GND@1 (-), C2.2, C3.2, C4.2, C5.2, CIN.2, CIN1.2, CIN2.2, CIN3.2, CIN4.2, CIN5.2, CIN6.2, CIN7.2, COUT.2, IC2.2 (GND), Q1.2 (E), R2.1, R3.2, R9.1, R13.1, R17.1, R22.1, RLIM.2, SENSE1.1, SENSE2.1, U$1.GND@1 (GND), U$1.GND@2 (GND), U$1.GND@3 (GND), U$1.GND@4 (GND), U$1.GND@5 (GND), U$1.GND@7 (GND), U$1.GND@8 (GND), U$1.GND@9 (GND), U$1.GND@10 (GND), U$1.GND@11 (GND), U$1.GND@12 (GND), U$1.GND@13 (GND), U$1.GND@14 (GND), U$1.GND@15 (GND), U$1.GND@16 (GND), U$1.GND@17 (GND), U$1.GND@26 (GND), U$2.5 (GND), U$2.6 (GND), U$4.2 (GND1), U$4.3 (GND2), U$4.7 (GND3), U$4.EXP (GNDPAD), U$5.PAD (GND), U$6.1 (GND), U$7.P$17 (DISTRI_GND), U$7.P$19 (DISTRI_GND), U$7.P$22 (DISTRI_GND), U$7.P$24 (DISTRI_GND), U$7.P$25 (DISTRI_GND), U$7.P$27 (DISTRI_GND), U$7.P$30 (DISTRI_GND), U$7.P$32 (DISTRI_GND), U$8.P$3 (VC1_CB), U$8.P$8 (GND), U$8.P$9 (PWR_PAD)
HEATER1: R5.1, R18.1, R19.1, R20.1
IN-OUT: CIN.1, CIN1.1, CIN3.1, IC2.1 (IN), R1.2, R6.2, R10.1, R11.1, R12.1, U$3.P$1 (1), U$4.1 (SENSE+), U$5.3 (VCC), U$5.4 (VCC2), U$5.5 (VCC3), U$7.P$18 (DISTRI_VBAT), U$7.P$20 (DISTRI_VBAT), U$7.P$21 (DISTRI_VBAT), U$7.P$23 (DISTRI_VBAT), U$7.P$26 (DISTRI_VBAT), U$7.P$28 (DISTRI_VBAT), U$7.P$29 (DISTRI_VBAT), U$7.P$31 (DISTRI_VBAT)
LDO-5V: CIN2.1, IC2.5 (OUT), R4.2, R21.2, U$6.4 (VDD)
LDO-EN: IC2.3 (!EN), R13.2, U$1.P2.5_GPIO, U$7.P$34
unnamed: C1.1, R7.1, U$8.P$1 (VC2)
unnamed: C1.2, C2.1, R8.1, U$8.P$2 (VC1)
unnamed: C3.1, RVD.1, U$8.P$6 (VDD)
unnamed: Q1.3 (C), R16.1
unnamed: C4.1, U$8.P$4 (CD)
unnamed: COUT.1, R5.2, R18.2, R19.2, R20.2, U$5.6 (VOUT3), U$5.7 (VOUT2), U$5.8 (VOUT)
unnamed: RLIM.1, U$5.10 (ILIM)
unnamed: SENSE1.2, U$6.2 (SENSE1)
unnamed: SENSE2.2, U$6.3 (SENSE2)
unnamed: U$1.P3.5_GPIO_DEBUG, U$2.8 (P3.5_GPIO_DEBUG)
unnamed: U$1.P3.4_GPIO_DEBUG, U$2.7 (P3.4_GPIO_DEBUG)
unnamed: U$1.P2.1_RXD, U$2.4 (P2.1_RXD)
unnamed: U$1.P2.0_TXD, U$2.3 (P2.0_TXD)
unnamed: U$1.SBWTDIO, U$2.2 (SBWTDIO)
unnamed: U$1.SBWTCK, U$2.SBWTCK
OUT: U$1.P1.6_GPIO/PWM, U$7.P$38, U$8.P$5 (OUT)
SCL: R11.2, U$1.P5.1_I2C-SCL-1, U$4.4 (SCL), U$7.P$33
SDA: R10.2, U$1.P5.0_I2C-SDA-1, U$4.5 (SDA), U$7.P$37
SYNC1: U$1.P7.2_SYNC1, U$7.P$45 (SYNC1)
SYNC2: U$1.PJ.3_SYNC2, U$7.P$49 (SYNC2)
TOVER: R4.1, U$1.P1.7_GPIO/PWM, U$5.2 (EN), U$6.6 (/TOVER/)
TRIP-TEST: R22.2, U$6.5 (TRIP-TEST)
V-BATT: BT1.PWR@1 (+), BT3.PWR@1 (+), R7.2, RVD.2, U$3.P$2 (2), U$4.8 (SENSE-)
VOLTAGE-ADC: C5.1, CIN6.1, R1.1, R2.2, U$1.P1.1_A1, U$7.P$42
VTEMP: CIN7.1, U$1.P1.0_A0, U$6.8 (VTEMP), U$7.P$35

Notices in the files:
parts and their libraries:
SparkFun-Connectors: Licensing: Creative Commons ShareAlike 4.0 International - https://creativecommons.org/licenses/by-sa/4.0
